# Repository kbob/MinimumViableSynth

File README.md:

# MinimumViableSynth

A virtual analog synthesizer with lots of knobs and buttons.

This is a polyphonic, monotimbral, virtual analog synth.  The audio
engine runs as an Apple Audio Unit on a Macintosh.  The control panel,
shown here, will provide dedicated controls for most of the synth's
functions.

The end goal is a self contained keyboard synth with knobs and buttons
with the classic connections: audio out, MIDI in/out, USB MIDI in/out.
I am getting there in three phases.

  * **Phase 1** (complete 2015-01-01): Softsynth.  The audio engine
    runs as an Audio Unit on a Mac.  It accepts MIDI messages and
    produces beautiful polyphonic analog sounds.  Or gritty,
    disturbing analog sounds.  It plugs in to DAW software (I use
    Logic Pro X).
    
  * **Phase 2** (in progress): Knobs and buttons.  I am designing and
    building a front panel (see above) with knobs, buttons, and an LCD
    touchscreen.  The goal is to make it as easy as possible to
    understand what the synth is doing at any time.

  * **Phase 3** (future): Stand-alone.  Build an enclosure that houses
    a keyboard, the knob and button panel, I/O jacks, and a processor
    (TBD) that can run the audio engine.  I'm looking at FPGAs...

## Why?

Learn stuff.  Music theory, DSP, PCB layout, CAD and machining, more.

## Status

Check out synth-notes.txt for my thoughts as I worked things out.

#### January 7, 2017:

I built 8 slave modules: the LFOs, the Controllers module, the
oscillators, the noise source, mixer, and filter.  I've since killed
the filter module, and one of the oscillators' LED has burnt out its
red component.  I have parts and tools to repair those; just haven't
done it yet.

I have working UI for the knobs and buttons.  Specifically, routing
between modulators and targets works, complete with lighting effects.

I made an enclosure from aluminum sheet and melamine end blocks, as
illustrated above.  It is flimsy, though, so that needs to be re-done.

I had the master, slaves, and LCD panel connected via a breadboard.
The breadboard wiring got flaky, so I stopped to design a PCB.  The
PCB snaps onto the back of the Discovery board, It routes video to the
LCD touch screen, SPI to the slaves, and serial MIDI to a future MIDI
I/O board.

I am currently designing the graphics for the LCD panel.

(Over a year since the last update.  Oops.)

#### December 17, 2015:

Three slave modules have been built.  (LFO1, LFO2, Controllers.)  All
the slave module PCBs are fabricated.

The master-slave communications are working over SPI.  The master
generates MIDI events.
[I can push a button on a slave and hear its effect on the audio
engine.](https://www.youtube.com/watch?v=dZsXk2Zf6Bg)

I blew up one of the LFO modules, probably with static discharge.  I
repaired it (swapped in a new Teensy LC), and it works now.  It was an
ugly repair.

Current tasks:

  + generating more MIDI events
  + experimenting with the LED animation
  + soldering up the rest of the slave modules
  + designing backing plates for the new slave modules

#### August 14, 2015:

The audio engine has been stable since January, though it does not
exactly match the front panel's feature set.

The front panel was fabricated in July.  I used a sheet of acrylic,
painted the underside black, then engraved the artwork through the
paint with a laser cutter.  Then the same laser cutter cut all the
holes for the controls.  It looks sharp, but not mass produced.
I got the work done at [InHaus Fabrication](http://inhausfabrication.com/).

There is a master microcontroller, an STM32F429, and each module has a
slave controller, a Teensy-LC.  Each slave directly drives a few
knobs, buttons, and LEDs.  The master will coordinate all the slaves
and provide the MIDI over USB interface.  I am currently writing SPI
drivers for master-slave communication.

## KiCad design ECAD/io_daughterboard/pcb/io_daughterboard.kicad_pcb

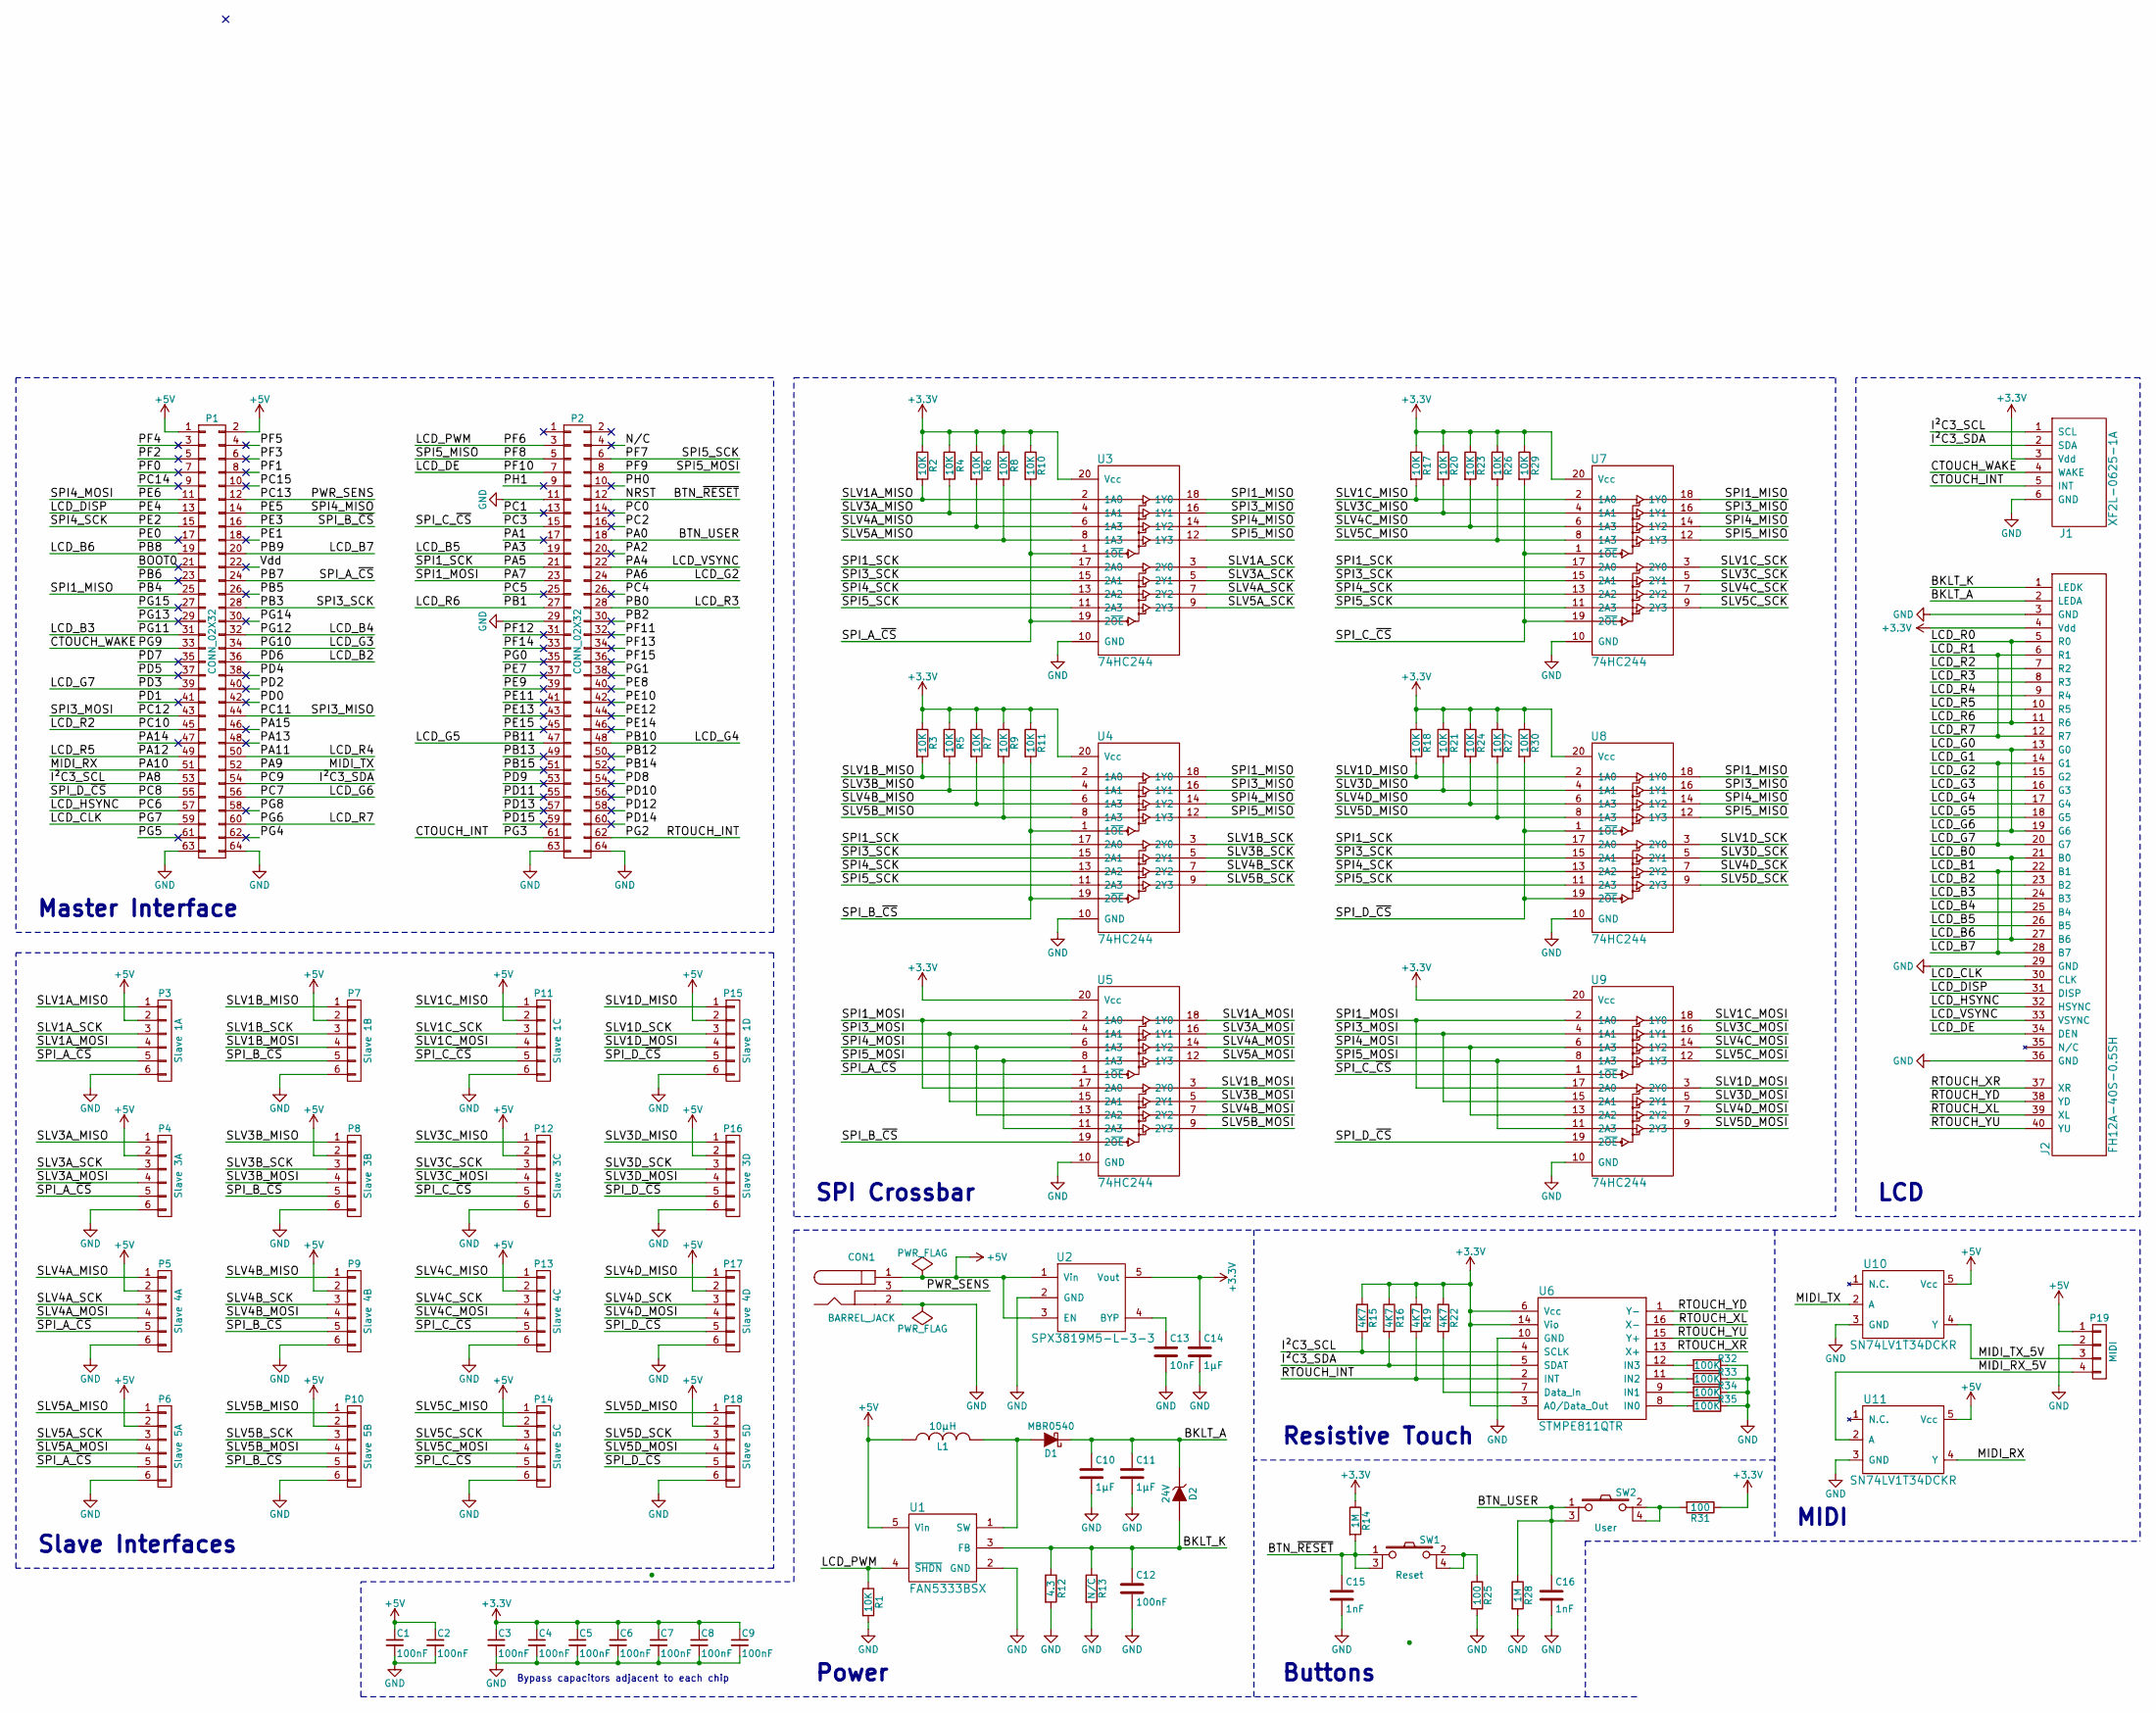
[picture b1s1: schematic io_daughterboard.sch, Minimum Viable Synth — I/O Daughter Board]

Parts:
C1, C2, C3, C4, C5, C6, C7, C8, C9, C12: 100nF; C_0603
C10, C11: 1µF; C_0805
C13: 10nF; C_0603
C14: 1µF; C_0603
C15, C16: 1nF; C_0603
CON1: BARREL_JACK
D1: MBR0540; SOD-123
D2: 24V; SOD-323
J1: XF2L-0625-1A; XF2L-0625
J2: FH12A-40S-0.5SH; FH12A-40S
L1: 10µH; Inductor_Taiyo-Yuden_NR-60xx
P1, P2: CONN_02X32; Socket_Strip_Reversed_2x32
P3: Slave 1A; Molex_PicoBlade_53047-0610_06x1.25mm_Straight
P4: Slave 3A; Molex_PicoBlade_53047-0610_06x1.25mm_Straight
P5: Slave 4A; Molex_PicoBlade_53047-0610_06x1.25mm_Straight
P6: Slave 5A; Molex_PicoBlade_53047-0610_06x1.25mm_Straight
P7: Slave 1B; Molex_PicoBlade_53047-0610_06x1.25mm_Straight
P8: Slave 3B; Molex_PicoBlade_53047-0610_06x1.25mm_Straight
P9: Slave 4B; Molex_PicoBlade_53047-0610_06x1.25mm_Straight
P10: Slave 5B; Molex_PicoBlade_53047-0610_06x1.25mm_Straight
P11: Slave 1C; Molex_PicoBlade_53047-0610_06x1.25mm_Straight
P12: Slave 3C; Molex_PicoBlade_53047-0610_06x1.25mm_Straight
P13: Slave 4C; Molex_PicoBlade_53047-0610_06x1.25mm_Straight
P14: Slave 5C; Molex_PicoBlade_53047-0610_06x1.25mm_Straight
P15: Slave 1D; Molex_PicoBlade_53047-0610_06x1.25mm_Straight
P16: Slave 3D; Molex_PicoBlade_53047-0610_06x1.25mm_Straight
P17: Slave 4D; Molex_PicoBlade_53047-0610_06x1.25mm_Straight
P18: Slave 5D; Molex_PicoBlade_53047-0610_06x1.25mm_Straight
P19: MIDI; Molex_PicoBlade_53047-0410_04x1.25mm_Straight
R1, R2, R3, R4, R5, R6, R7, R8, R9, R10, R11, R17, R18, R20, R21, R23, R24, R26, R27, R29, R30: 10K; R_0603
R12: 4.3; R_0603_HandSoldering
R13: N/C; R_0603_HandSoldering_no_paste
R14, R28: 1M; R_0603
R15, R16, R19, R22: 4K7; R_0603
R25, R31: 100; R_0603
R32, R33, R34, R35: 100K; R_0603
SW1: Reset; WS-TASV
SW2: User; WS-TASV
U1: FAN5333BSX; SOT-23-5
U2: SPX3819M5-L-3-3; SOT-23-5
U3, U4, U5, U7, U8, U9: 74HC244; TSSOP-20_4.4x6.5mm_Pitch0.65mm
U6: STMPE811QTR; QFN-16-1EP_3x3mm_Pitch0.5mm
U10, U11: SN74LV1T34DCKR; SOT-23-5

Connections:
+3V3: C3.1, C4.1, C5.1, C6.1, C7.1, C8.1, C9.1, C14.1, J1.3 (Vdd), J2.4 (Vdd), R2.1, R3.1, R4.1, R5.1, R6.1, R7.1, R8.1, R9.1, R10.1, R11.1, R14.1, R15.1, R16.1, R17.1, R18.1, R19.1, R20.1, R21.1, R22.1, R23.1, R24.1, R26.1, R27.1, R29.1, R30.1, R31.1, U2.5 (Vout), U3.20 (Vcc), U4.20 (Vcc), U5.20 (Vcc), U6.3 (A0/Data_Out), U6.6 (Vcc), U6.14 (Vio), U7.20 (Vcc), U8.20 (Vcc), U9.20 (Vcc)
+5V: C1.1, C2.1, CON1.1, L1.1, P1.1, P1.2, P3.2, P4.2, P5.2, P6.2, P7.2, P8.2, P9.2, P10.2, P11.2, P12.2, P13.2, P14.2, P15.2, P16.2, P17.2, P18.2, P19.1, U1.5 (Vin), U2.1 (Vin), U2.3 (EN), U10.5 (Vcc), U11.5 (Vcc)
/BKLT_A: C10.1, C11.1, D1.1 (K), D2.1 (K), J2.2 (LEDA)
/BKLT_K: C12.1, D2.2 (A), J2.1 (LEDK), R12.1, R13.1, U1.3 (FB)
/BOOT0: P1.21
/BTN_USER: C16.1, P2.18, R28.1, SW2.1, SW2.3
/BTN_~RESET: C15.1, P2.12, R14.2, SW1.1, SW1.3
/CTOUCH_INT: J1.5 (INT), P2.61
/CTOUCH_WAKE: J1.4 (WAKE), P1.33
/I²C3_SCL: J1.1 (SCL), P1.53, R15.2, U6.4 (SCLK)
/I²C3_SDA: J1.2 (SDA), P1.54, R16.2, U6.5 (SDAT)
/LCD_B0: J2.21 (B0), J2.27 (B6), P1.19
/LCD_B1: J2.22 (B1), J2.28 (B7), P1.20
/LCD_B2: J2.23 (B2), P1.36
/LCD_B3: J2.24 (B3), P1.31
/LCD_B4: J2.25 (B4), P1.32
/LCD_B5: J2.26 (B5), P2.19
/LCD_CLK: J2.30 (CLK), P1.59
/LCD_DE: J2.34 (DEN), P2.7
/LCD_DISP: J2.31 (DISP), P1.13
/LCD_G0: J2.13 (G0), J2.19 (G6), P1.56
/LCD_G1: J2.14 (G1), J2.20 (G7), P1.39
/LCD_G2: J2.15 (G2), P2.24
/LCD_G3: J2.16 (G3), P1.34
/LCD_G4: J2.17 (G4), P2.48
/LCD_G5: J2.18 (G5), P2.47
/LCD_HSYNC: J2.32 (HSYNC), P1.57
/LCD_PWM: P2.3, R1.1, U1.4 (~SHDN)
/LCD_R0: J2.5 (R0), J2.11 (R6), P2.27
/LCD_R1: J2.6 (R1), J2.12 (R7), P1.60
/LCD_R2: J2.7 (R2), P1.45
/LCD_R3: J2.8 (R3), P2.28
/LCD_R4: J2.9 (R4), P1.50
/LCD_R5: J2.10 (R5), P1.49
/LCD_VSYNC: J2.33 (VSYNC), P2.22
/MIDI_RX: P1.51, U11.4 (Y)
/MIDI_RX_5V: P19.4, U11.2 (A)
/MIDI_TX: P1.52, U10.2 (A)
/MIDI_TX_5V: P19.3, U10.4 (Y)
/N/C: P2.4
/PA1: P2.17
/PA2: P2.20
/PA5: P2.21, U3.17 (2A0), U4.17 (2A0), U7.17 (2A0), U8.17 (2A0)
/PA7: P2.23, U5.2 (1A0), U5.17 (2A0), U9.2 (1A0), U9.17 (2A0)
/PA13: P1.48
/PA14: P1.47
/PA15: P1.46
/PB2: P2.30
/PB3: P1.28, U3.15 (2A1), U4.15 (2A1), U7.15 (2A1), U8.15 (2A1)
/PB4: P1.25, U3.18 (1Y0), U4.18 (1Y0), U7.18 (1Y0), U8.18 (1Y0)
/PB5: P1.26
/PB6: P1.23
/PB7: P1.24, P3.5, P4.5, P5.5, P6.5, R10.2, U3.1 (1~OE), U3.19 (2~OE), U5.1 (1~OE)
/PB12: P2.50
/PB13: P2.49
/PB14: P2.52
/PB15: P2.51
/PC0: P2.14
/PC1: P2.13
/PC2: P2.16
/PC3: P2.15, P11.5, P12.5, P13.5, P14.5, R29.2, U7.1 (1~OE), U7.19 (2~OE), U9.1 (1~OE)
/PC4: P2.26
/PC5: P2.25
/PC8: P1.55, P15.5, P16.5, P17.5, P18.5, R30.2, U8.1 (1~OE), U8.19 (2~OE), U9.19 (2~OE)
/PC11: P1.44, U3.16 (1Y1), U4.16 (1Y1), U7.16 (1Y1), U8.16 (1Y1)
/PC12: P1.43, U5.4 (1A1), U5.15 (2A1), U9.4 (1A1), U9.15 (2A1)
/PC13: CON1.3, P1.12
/PC14: P1.9
/PC15: P1.10
/PD0: P1.42
/PD1: P1.41
/PD2: P1.40
/PD4: P1.38
/PD5: P1.37
/PD7: P1.35
/PD8: P2.54
/PD9: P2.53
/PD10: P2.56
/PD11: P2.55
/PD12: P2.58
/PD13: P2.57
/PD14: P2.60
/PD15: P2.59
/PE0: P1.17
/PE1: P1.18
/PE2: P1.15, U3.13 (2A2), U4.13 (2A2), U7.13 (2A2), U8.13 (2A2)
/PE3: P1.16, P7.5, P8.5, P9.5, P10.5, R11.2, U4.1 (1~OE), U4.19 (2~OE), U5.19 (2~OE)
/PE5: P1.14, U3.14 (1Y2), U4.14 (1Y2), U7.14 (1Y2), U8.14 (1Y2)
/PE6: P1.11, U5.6 (1A3), U5.13 (2A2), U9.6 (1A3), U9.13 (2A2)
/PE7: P2.37
/PE8: P2.40
/PE9: P2.39
/PE10: P2.42
/PE11: P2.41
/PE12: P2.44
/PE13: P2.43
/PE14: P2.46
/PE15: P2.45
/PF0: P1.7
/PF1: P1.8
/PF2: P1.5
/PF3: P1.6
/PF4: P1.3
/PF5: P1.4
/PF7: P2.6, U3.11 (2A3), U4.11 (2A3), U7.11 (2A3), U8.11 (2A3)
/PF8: P2.5, U3.12 (1Y3), U4.12 (1Y3), U7.12 (1Y3), U8.12 (1Y3)
/PF9: P2.8, U5.8 (1A3), U5.11 (2A3), U9.8 (1A3), U9.11 (2A3)
/PF11: P2.32
/PF12: P2.31
/PF13: P2.34
/PF14: P2.33
/PF15: P2.36
/PG0: P2.35
/PG1: P2.38
/PG2: P2.62, R19.2, U6.2 (INT)
/PG4: P1.62
/PG5: P1.61
/PG8: P1.58
/PG13: P1.29
/PG14: P1.30
/PG15: P1.27
/PH0: P2.10
/PH1: P2.9
/RTOUCH_XL: J2.39 (XL), U6.16 (X-)
/RTOUCH_XR: J2.37 (XR), U6.13 (X+)
/RTOUCH_YD: J2.38 (YD), U6.1 (Y-)
/RTOUCH_YU: J2.40 (YU), U6.15 (Y+)
/SLV1A_MISO: P3.1, R2.2, U3.2 (1A0)
/SLV1A_MOSI: P3.4, U5.18 (1Y0)
/SLV1A_SCK: P3.3, U3.3 (2Y0)
/SLV1B_MISO: P7.1, R3.2, U4.2 (1A0)
/SLV1B_MOSI: P7.4, U5.3 (2Y0)
/SLV1B_SCK: P7.3, U4.3 (2Y0)
/SLV1C_MISO: P11.1, R17.2, U7.2 (1A0)
/SLV1C_MOSI: P11.4, U9.18 (1Y0)
/SLV1C_SCK: P11.3, U7.3 (2Y0)
/SLV1D_MISO: P15.1, R18.2, U8.2 (1A0)
/SLV1D_MOSI: P15.4, U9.3 (2Y0)
/SLV1D_SCK: P15.3, U8.3 (2Y0)
/SLV3A_MISO: P4.1, R4.2, U3.4 (1A1)
/SLV3A_MOSI: P4.4, U5.16 (1Y1)
/SLV3A_SCK: P4.3, U3.5 (2Y1)
/SLV3B_MISO: P8.1, R5.2, U4.4 (1A1)
/SLV3B_MOSI: P8.4, U5.5 (2Y1)
/SLV3B_SCK: P8.3, U4.5 (2Y1)
/SLV3C_MISO: P12.1, R20.2, U7.4 (1A1)
/SLV3C_MOSI: P12.4, U9.16 (1Y1)
/SLV3C_SCK: P12.3, U7.5 (2Y1)
/SLV3D_MISO: P16.1, R21.2, U8.4 (1A1)
/SLV3D_MOSI: P16.4, U9.5 (2Y1)
/SLV3D_SCK: P16.3, U8.5 (2Y1)
/SLV4A_MISO: P5.1, R6.2, U3.6 (1A3)
/SLV4A_MOSI: P5.4, U5.14 (1Y2)
/SLV4A_SCK: P5.3, U3.7 (2Y2)
/SLV4B_MISO: P9.1, R7.2, U4.6 (1A3)
/SLV4B_MOSI: P9.4, U5.7 (2Y2)
/SLV4B_SCK: P9.3, U4.7 (2Y2)
/SLV4C_MISO: P13.1, R23.2, U7.6 (1A3)
/SLV4C_MOSI: P13.4, U9.14 (1Y2)
/SLV4C_SCK: P13.3, U7.7 (2Y2)
/SLV4D_MISO: P17.1, R24.2, U8.6 (1A3)
/SLV4D_MOSI: P17.4, U9.7 (2Y2)
/SLV4D_SCK: P17.3, U8.7 (2Y2)
/SLV5A_MISO: P6.1, R8.2, U3.8 (1A3)
/SLV5A_MOSI: P6.4, U5.12 (1Y3)
/SLV5A_SCK: P6.3, U3.9 (2Y3)
/SLV5B_MISO: P10.1, R9.2, U4.8 (1A3)
/SLV5B_MOSI: P10.4, U5.9 (2Y3)
/SLV5B_SCK: P10.3, U4.9 (2Y3)
/SLV5C_MISO: P14.1, R26.2, U7.8 (1A3)
/SLV5C_MOSI: P14.4, U9.12 (1Y3)
/SLV5C_SCK: P14.3, U7.9 (2Y3)
/SLV5D_MISO: P18.1, R27.2, U8.8 (1A3)
/SLV5D_MOSI: P18.4, U9.9 (2Y3)
/SLV5D_SCK: P18.3, U8.9 (2Y3)
/Vdd: P1.22
GND: C1.2, C2.2, C3.2, C4.2, C5.2, C6.2, C7.2, C8.2, C9.2, C10.2, C11.2, C12.2, C13.2, C14.2, C15.2, C16.2, CON1.2, J1.6 (GND), J2.3 (GND), J2.29 (GND), J2.36 (GND), P1.63, P1.64, P2.11, P2.29, P2.63, P2.64, P3.6, P4.6, P5.6, P6.6, P7.6, P8.6, P9.6, P10.6, P11.6, P12.6, P13.6, P14.6, P15.6, P16.6, P17.6, P18.6, P19.2, R1.2, R12.2, R13.2, R25.2, R28.2, R32.1, R33.1, R34.1, R35.1, U1.2 (GND), U2.2 (GND), U3.10 (GND), U4.10 (GND), U5.10 (GND), U6.10 (GND), U7.10 (GND), U8.10 (GND), U9.10 (GND), U10.3 (GND), U11.3 (GND)
unnamed: C13.1, U2.4 (BYP)
unnamed: D1.2 (A), L1.2, U1.1 (SW)
unnamed: R22.2, U6.7 (Data_In)
unnamed: R25.1, SW1.2, SW1.4
unnamed: R31.2, SW2.2, SW2.4
unnamed: R32.2, U6.12 (IN3)
unnamed: R33.2, U6.11 (IN2)
unnamed: R34.2, U6.9 (IN1)
unnamed: R35.2, U6.8 (IN0)

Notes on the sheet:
Master Interface
Power
SPI Crossbar
Resistive Touch
MIDI
Slave Interfaces
Buttons
LCD
Bypass capacitors adjacent to each chip

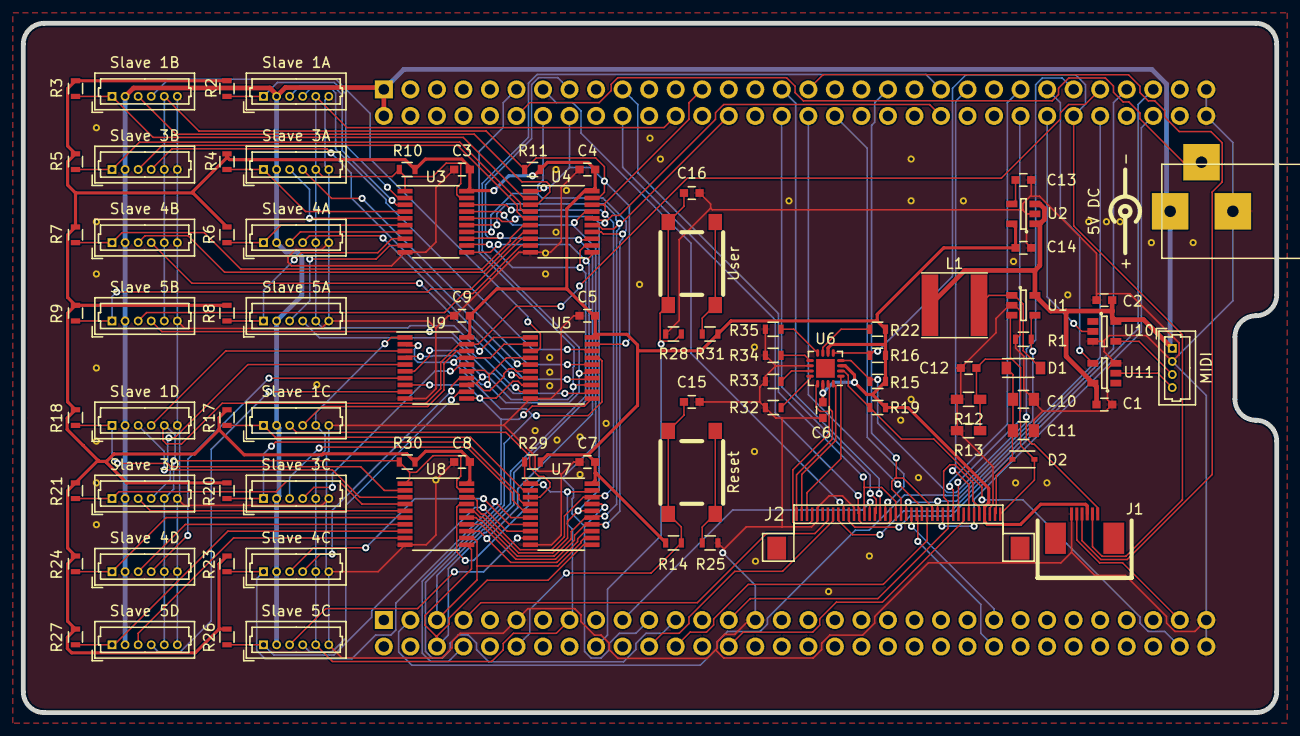
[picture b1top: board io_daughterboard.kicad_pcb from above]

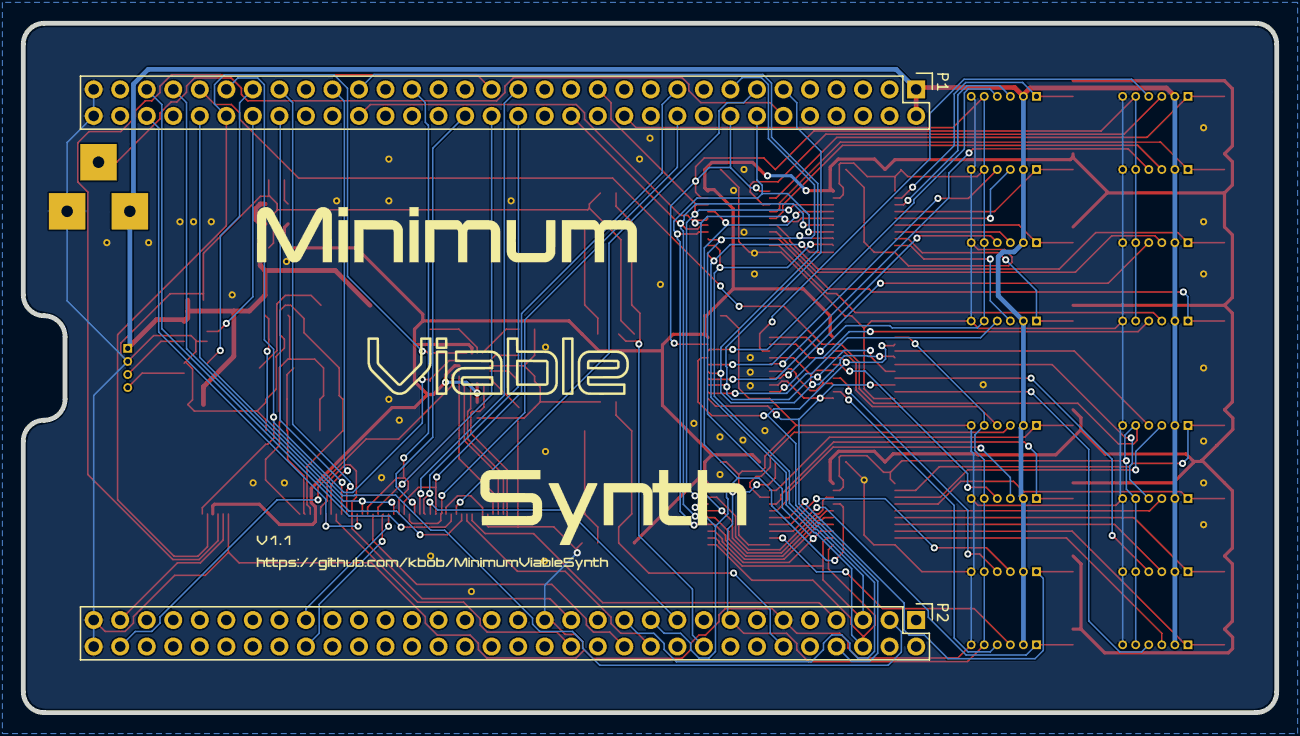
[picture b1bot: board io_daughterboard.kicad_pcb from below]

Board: 2 copper layers, 120.0 x 66.0 mm, 89 parts (2 on the bottom side), 118 nets.

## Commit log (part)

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2014-11-19 Minimum Viable Synth. Mostly works. Some parameters' scales are wrong.
2014-11-19 Implement velocity, fixup parameters.
2014-11-19 Still just cosmetic. Indentation, comments, removed unused method MVS::GetControls().
2014-11-20 More cleanup. Removed DEBUG_PRINT, removed no-op MVSNote::Kill() method, cleaned up MVSNote::Render().
2014-11-22 Globally renamed MVS to MVS 2. Now has sine, sawtooth, triangle, square, and pulse waveforms with continuous waveform modulation under MIDI control.
2014-11-29 Increased maximum number of voices to 18.
2014-11-29 Now ⌘-B create Release build. Needed so the decimation filter will vectorize.
2014-11-29 Now the synth runs with 4× oversampling.
2014-11-29 Enabled Triangle waveform. Changed direction of triangle skew to match sawtooth.
2014-11-29 Removed zipper noise when quickly modulating square wave pulse width.
2014-11-30 Increased max polyphony to 500. Changed ADSR time parameters to allow range of 0 .. 10 seconds with cube root display.
2014-12-01 Implemented exponential envelopes. Now uses exponential envelope for note amplitude.
2014-12-04 Now has two oscillators.
2014-12-10 Separated Oscillator 2's detune parameter into coarse and fine parts.
2014-12-15 Renamed MVS 3 to MVS 4.
2014-12-15 Silenced all compiler warnings.
2014-12-19 New parameter infrastructure. Removed vibrato and noise envelope. Needs much cleanup, but checking now because it's in a working state.
2014-12-19 Much cleanup. Removed dead code from old parameter infrastructure.
2014-12-20 Commented out a lot of unimplemented parameters. Renamed Oscillator::Type to Oscillator::Waveform.
2014-12-20 New ModWheel module gives smoothed Modulation Wheel data. Plumbing to get modulation to MVSNotes.
2014-12-21 Interim version. Working toward a full modulation matrix.
2014-12-24 Modulation matrix implemented. Changing a destination parameter updates the modulation matrix.
2014-12-25 Modulation matrix mostly implemented. Modulation sources ModWheel, LFO1, LFO2, several destinations. Also implemented ring modulator and hard sync.
2014-12-30 Now you can turn the (nonexistent) filter off, and Osc 2 detune has been adjusted to work better with the range of MIDI controllers (0..127).
2014-12-31 Tweaked parameter limits to play better with AU Lab's MIDI interface. I think AU Lab is wrong, but I'll conform anyway.
2015-01-01 New envelopes. Parameters are fully modulable. Also new Amplifier component -- the former AmpEnv has been decomposed.
2015-01-01 Finished renaming Modwheel files to ModWheel.
2015-01-01 Added comments to delineate the sections in MVSParamSet::MVSParamSet().
2015-01-01 Fixed Envelope 2 amount control.
2015-01-02 Ring Modulator volume now depends only on Oscillator 1 volume. The other way was too error prone.
2015-01-02 Implemented filter keytracking.
2015-01-02 Implemented key tracking for Envelope 2.
2015-01-04 Now restores user presets.
2015-01-04 Now has a factory preset.
2015-01-10 Continued tweaking parameters, now passes AU validation.
2015-01-12 AU Lab bug compatibility is now wrapped in AULAB_BUG_COMPAT. When undefined, synth works with Logic Pro X.
2015-01-15 Created a separate build target for the Logic Pro version.
2015-01-15 Added new target: MVS 4 - AU Lab.
2015-05-29 Moved audio units into the Audio Unit subdirectory.
2015-05-29 Imported Eagle CAD files. They probably don't build in this environment.
2015-05-29 Checked in the LFO substrate mechanical CAD drawing.
2015-05-30 synth-dsl.py generates the front panel.
2015-05-31 Removed some unneeded switch devices, added a SPI jumper (unfinished).
2015-05-31 Everything.sch - a template module schematic with the union of all circuits
2015-05-31 synth-notes.txt - I've been taking notes for the last 8 months.
2015-05-31 embiggen-filter.py - rewrite filter.brd to actual size, since the Eagle file is compressed.
2015-05-31 Aaaauurghh! Misspelled "Minimum Viable Synth"!
2015-05-31 Fixed a skewed wire.
2015-05-31 Two more PCBs: Oscillator and Duo (the two-control board).
2015-05-31 ... still renaming "LFO Small" to "LFO".
2015-05-31 Moved the LED bar graphs' color labels to the silkscreen layer.
2015-05-31 ... testing on repo ...
2015-05-31 Ignore emacs temp files.
2015-05-31 Starting to design the envelope control boards
2015-05-31 This is the filter board, with the controls spaced out to the right positions.
2015-05-31 Added brief description and status.
2015-05-31 misc. updates
2015-05-31 1.0 versions of the Filter, Oscillator, and Duo boards sent to OSHPark and archived.
2015-06-01 Designed the Envelope board. Fairly straightforward, except that it has three variants.
2015-06-01 Envelope and Master Volume 1.0 archived and sent to fab.
2015-06-01 LFO substrate: more clearance around SPI header, single top clip, strain relief in spine.
2015-06-09 Changed based on Kris@inhausfabrication.com's suggestions
2015-06-09 Initial checkin of master firmware. USB MIDI works, SPI works.
2015-06-09 Documented the protocol between master and slave.
2015-06-09 Archive copies of files sent for laser cutting
2015-06-11 Changes based on first lasercut prototypes. More coming.
2015-06-11 Made the envelope filter destination arrow swoopy.
2015-06-15 Added cmd line args to select the different output modes.
2015-06-15 Shell script renders all the different front panel files.
2015-06-15 Archived v0.3 front panel files, as they've been sent to fab.
2015-06-21 Variant LFO substrate is thicker to clear power jumpers.
2015-07-31 Fixed panel size calculation for paginated output.
2015-08-09 Added const declarations where appropriate.
2015-08-09 Master now transmits SPI data using DMA.
2015-08-09 Cleaned up SPI DMA in SPI-master firmware.
2015-08-10 GPIO cleanup.
2015-08-10 Cut over all modules to new GPIO API.
2015-08-17 Now draws module destination arrows in artwork mode.
2015-08-17 Updated README.
2015-08-17 Implemented synth_config and synth_state data structures.
2015-08-17 Checked in the wrong file.
2015-08-20 Just added a comment.
2015-08-20 Made module and knob index symbols public. Created module/knob config flags.
2015-08-20 Started defining factory defaults. Got bogged down thinking about how the Controllers module will work.
2015-08-20 Preliminary thoughts about the Controllers module.
2015-11-26 Unknown changes.
2015-11-26 Now Master sends well-formed messages to Slave(s).
2015-11-30 Slave firmware serial port use is #ifdef'd out.
2015-11-30 Increased system clock to 50 Hz, SPI clock to 600 Hz.
2015-11-30 Fixed stupid bug in Fletcher-16 checksum.
2015-11-30 Now runs at full speed: SPI clock ~5 MHz, system tick 1 msec.
2015-12-02 Moved SPI group B select from pin PA9 to PC13. Conflict on PA9.
2015-12-06 Outlined APIs for MIDI, USB, and SPI drivers.
2015-12-06 MIDI API defined.
2015-12-06 Now draws the modules in color.
2015-12-06 Now SPI DMA interrupts on completion.
2015-12-09 Lots of cleanup.
2015-12-09 Still tweaking the colors.
2015-12-10 Now one button works end to end. Press a Choice button; send a MIDI CC message.
2015-12-10 Button notes use real MIDI API.
2015-12-18 First status update in 4 months.
2015-12-18 Updated front page picture.
2015-12-20 Now prints a helpful message if $LIBOPENCM3 is undefined.
2015-12-21 Updated to XCode 7.2. Fixed bug in enum params > 10 states.
2015-12-22 Designed substrates to hold up several slave boards.
2015-12-22 Added strain relief slots to the filter substrate.
2015-12-22 Assign button is dark when source is unassigned.
2015-12-22 Tweaked clearance for Teensy.
2016-01-17 Started adding datasheets for parts used.
2016-01-17 OpenSCAD animation of how to assemble the parts.
2016-01-17 Re-rendered assembly GIF with perspective view.
2016-01-17 Changed the button to drop every 6th note by 3 octaves.
2016-01-17 Filter has 3 choices, not 6.
2016-01-17 Fixed sequence error with multiple SPI buses active.
2016-01-17 Added code to show back panel jack positions.
2016-01-18 Described enclosure plans.
2016-01-27 Made a plastic plug to fit in the end of the case.
2016-01-27 Sample graphics image and RLE compiler for graphics test.
2016-02-06 Added plate to screw on end cap.
2016-02-06 Keep tweaking geometry until it fits.
2016-02-06 Enable the first eight modules.
2016-02-06 Added LCD-TFT and SDRAM drivers.
2016-02-06 Added speed and type to gpio pins, cleaned up gpio pin init.
2016-02-07 Clean up GPIO init.
2016-02-10 Changed group B slave select again to PE3.
2016-02-10 Ugh.
2016-02-11 Removed dead code from lcd-dma.c.
2016-02-11 Slave self-test no longer leaves extra choice LEDs on.
2016-02-17 Conditioned analog inputs to avoid spurious movement.
2016-02-17 Recorded issues fixed.
2016-02-22 Fixed LCD-TFT startup.
2016-03-25 Re-enabled printing bad packets.
2016-03-25 Added statistics to USB-MIDI.
2016-03-25 Created WITH_INTERRUPTS_MASKED module.
2016-03-25 Removed junk.
2016-08-17 Now compiles both binary and include files formats.
2016-11-08 New synth notes. Starting to plan out I/O daughtercard.
2016-11-09 Moved module PCBs to ECAD/modules/.
2016-11-10 Started I/O Daughter Board. Collected data sheets.
2016-11-11 Major components are in the schematic.
2016-11-12 annotated the P1 connector.
2016-11-12 Tweaked P1 pins 1-16.
2016-11-12 Annotated P2 pins.
2016-11-13 Preliminary notes on the MIDI board.
2016-11-13 Capacitive touch connector.
2016-11-14 Should not have committed backup file.
2016-11-14 Schematic for backlight power supply drawn.
2016-11-14 added slave connectors to schematic; laid out page.
2016-11-14 More schematic tweaks.
2016-11-16 Fixed 10 errors on schematic. Still no power flags.
2016-11-16 spello.
2016-11-16 Schematic annotated and electrical rules checked.
2016-11-16 Added footprints for the easy components.
2016-11-18 Drew and dimensioned board outline.
2016-11-18 Flipped board to make LCD right side up. Regenerated netlist with footprints.
2016-11-18 git ignore *-rescue.lib.
2016-11-18 Changed values of slave connectors to "Slave 1A" etc.
2016-11-21 P1 and P2 connectors placed. Back to PicoBlade through-hole connectors.
2016-11-21 Placed J1 and J2 FPC connectors.
2016-11-21 Ignore KiCad .rpt files.
2016-11-22 All components are on the board.
2016-11-22 Ready to autoroute?
2016-11-22 Repositioned RTOUCH circuit.
2016-11-23 Try moving the SPI buffers around. Manually route bypass caps.
2016-11-23 Moved reset button resistors.
2016-11-23 Freerouting rules and configuration.
2016-11-23 Board autorouted, DRC and missing connections fixed.
2016-11-25 Working on BOM.
2016-11-27 Re-autorouted with no ground plane.
2016-11-27 Cleaned up silkscreen.
2016-11-28 Added logo to back of board.
2016-11-29 Widened ground traces failed DRC.
2016-11-29 The footprint for the no-solder resistor
2016-11-29 Switched connectors P1 and P2. Made traces for filter caps.
2016-11-29 Re-routed board with P1/P2 corrected, added explicit ground-to-bypass traces.
2016-11-29 Added ground plane; widened ground traces to slave connectors.
2016-11-29 Improved ground plane around slave connectors.
2016-12-17 Created stuffing guide.
2016-12-17 Updated datasheets.
2016-12-17 Removed all traces and vias (again).
2016-12-17 Changed solder mask clearance to 0.05 mm. (Grrr!)
2016-12-17 Changed LCD connector to Hirose FH12A.
2016-12-18 Fixed arrowhead.
2016-12-18 Routed board. Same as always - no ground pour, three trace sizes.
2016-12-18 Typo in comment.
2016-12-19 Changed barrel jack hole sizes to 1.1mm.
2016-12-19 Disconnected +3.3V from P2.
2016-12-19 Removed all traces and copper pours; reconnected filter caps.
2016-12-19 git ignore *.kicad_pcb.orig files.
2016-12-20 Added copper pours front and back for ground.
2017-01-06 Video works with I/O daughterboard and 5" LCD-TFT screen.
